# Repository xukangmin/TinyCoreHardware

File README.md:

# TinyCoreHardware
Hardware Files for Tiny Core

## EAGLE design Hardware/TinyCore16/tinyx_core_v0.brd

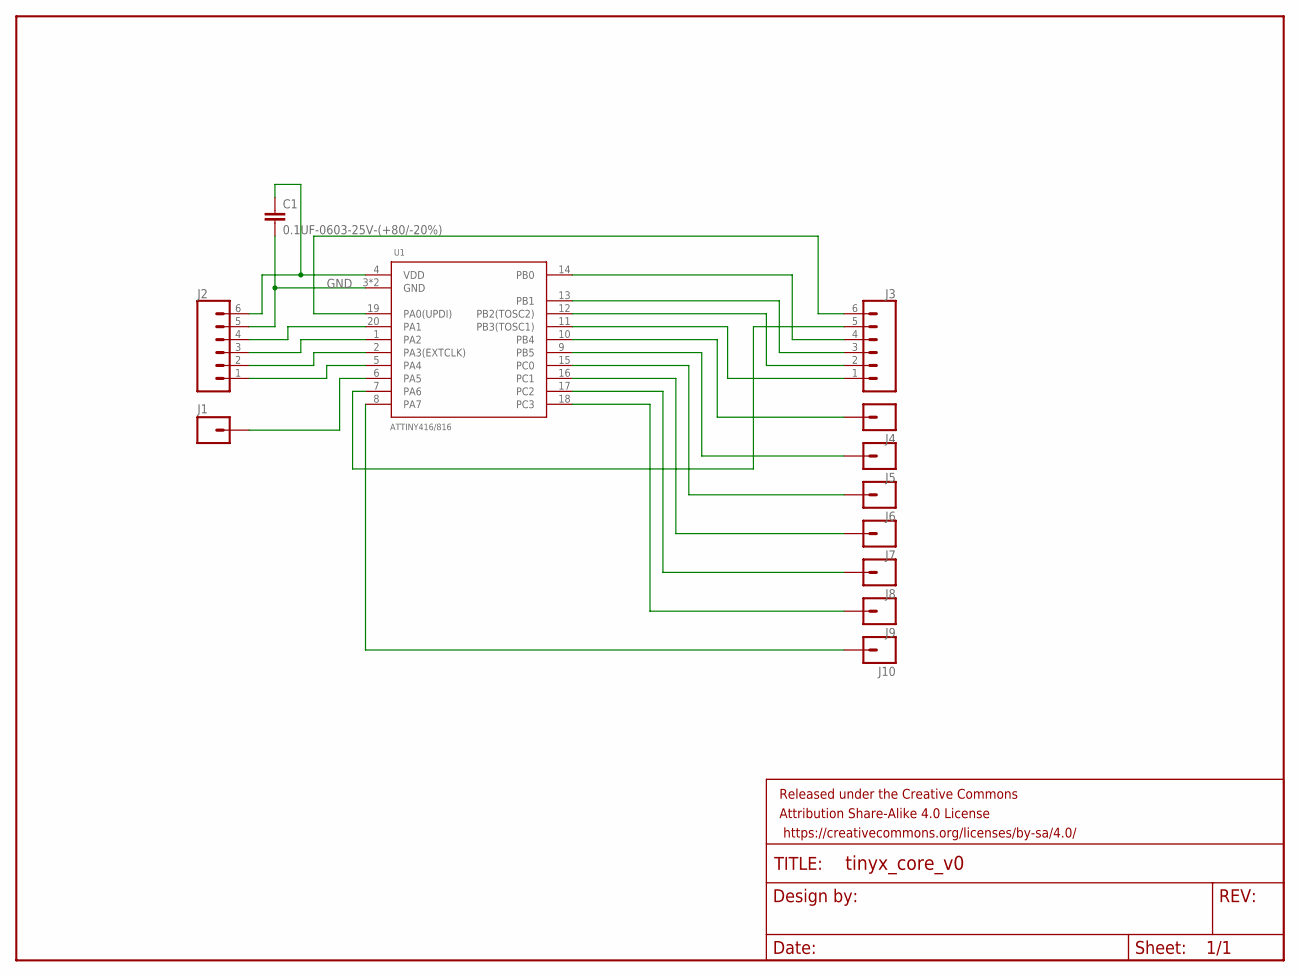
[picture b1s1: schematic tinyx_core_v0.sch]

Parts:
C1: 0.1UF-0603-25V-(+80/-20%); 0603
FRAME1: FRAME-LETTER; CREATIVE_COMMONS
J1, J4, J5, J6, J7, J8, J9, J10: M01TINY; 1X01_TINY
J2, J3: CONN_06NO_SILK_FEMALE_PTH; 1X06_NO_SILK
U1: ATTINY416/816; VQFN-20

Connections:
GND: C1.2, J2.5, U1.3 (GND), U1.EXP (GND)
unnamed: C1.1, J2.6, U1.4 (VDD)
unnamed: J2.4, U1.20 (PA1)
unnamed: J2.3, U1.1 (PA2)
unnamed: J2.2, U1.2 (PA3(EXTCLK))
unnamed: J2.1, U1.5 (PA4)
unnamed: J3.6, U1.19 (PA0(UPDI))
unnamed: J3.5, U1.7 (PA6)
unnamed: J3.4, U1.14 (PB0)
unnamed: J3.3, U1.13 (PB1)
unnamed: J3.2, U1.12 (PB2(TOSC2))
unnamed: J3.1, U1.11 (PB3(TOSC1))
unnamed: J1.P$1, U1.6 (PA5)
unnamed: J4.P$1, U1.10 (PB4)
unnamed: J5.P$1, U1.9 (PB5)
unnamed: J6.P$1, U1.15 (PC0)
unnamed: J7.P$1, U1.16 (PC1)
unnamed: J8.P$1, U1.17 (PC2)
unnamed: J9.P$1, U1.18 (PC3)
unnamed: J10.P$1, U1.8 (PA7)

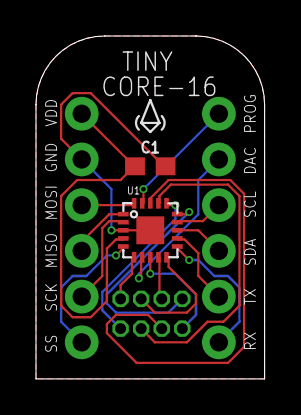
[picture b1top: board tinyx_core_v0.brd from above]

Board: 2 copper layers, 12.7 x 19.1 mm, 13 parts (0 on the bottom side), 20 nets.

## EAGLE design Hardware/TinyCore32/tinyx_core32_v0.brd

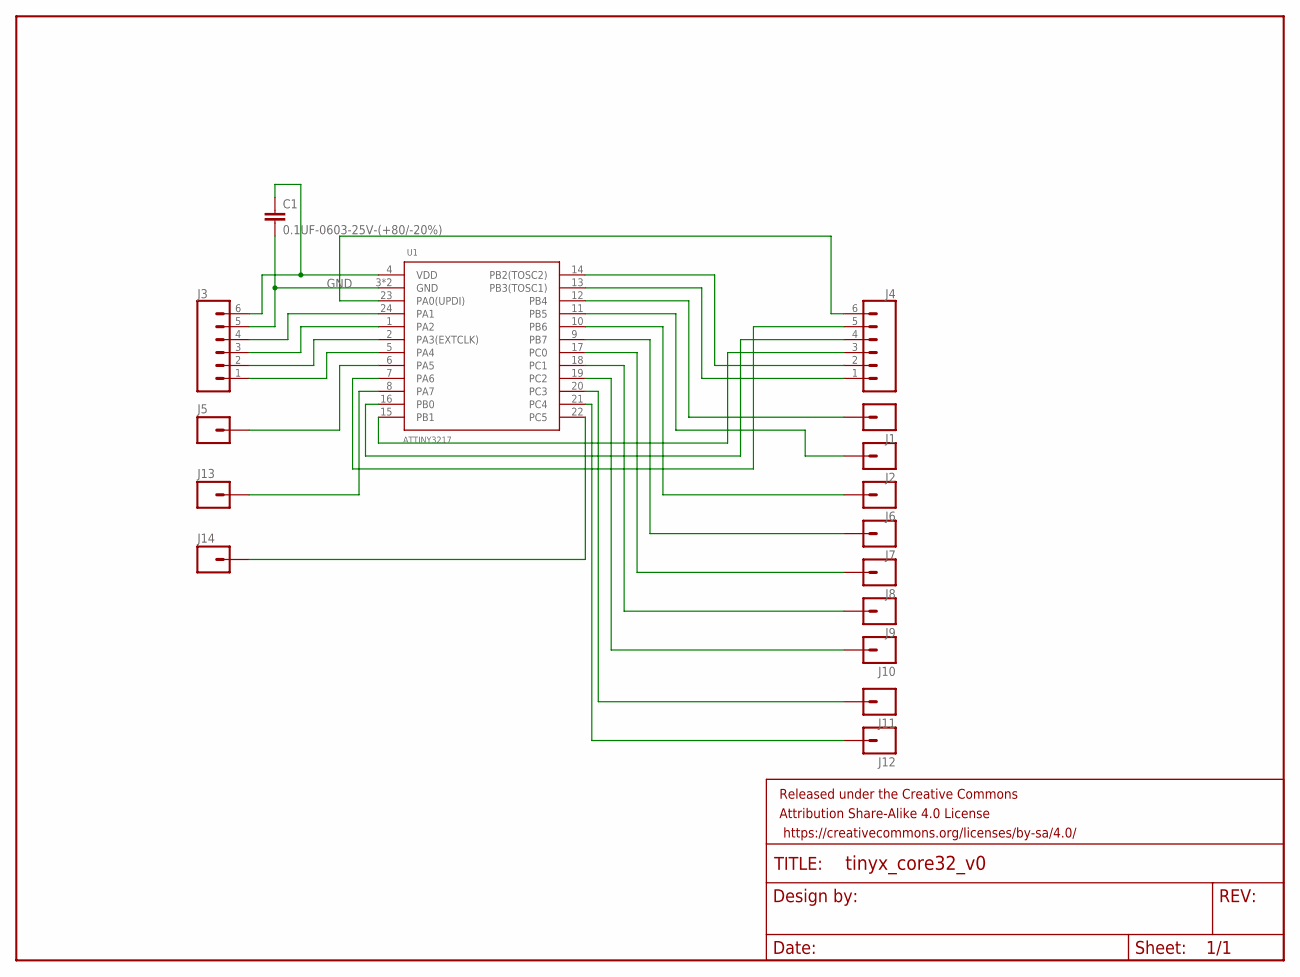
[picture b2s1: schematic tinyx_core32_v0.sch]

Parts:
C1: 0.1UF-0603-25V-(+80/-20%); 0603
FRAME1: FRAME-LETTER; CREATIVE_COMMONS
J1, J2, J5, J6, J7, J8, J9, J10, J11, J12, J13, J14: M01TINY; 1X01_TINY
J3, J4: CONN_06NO_SILK_NO_POP; 1X06_NO_SILK
U1: ATTINY3217; VQFN-24-N

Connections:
GND: C1.2, J3.5, U1.3 (GND), U1.P$1 (GND)
unnamed: C1.1, J3.6, U1.4 (VDD)
unnamed: J3.4, U1.24 (PA1)
unnamed: J3.3, U1.1 (PA2)
unnamed: J3.2, U1.2 (PA3(EXTCLK))
unnamed: J3.1, U1.5 (PA4)
unnamed: J4.6, U1.23 (PA0(UPDI))
unnamed: J1.P$1, U1.12 (PB4)
unnamed: J4.5, U1.7 (PA6)
unnamed: J4.4, U1.16 (PB0)
unnamed: J4.3, U1.15 (PB1)
unnamed: J4.2, U1.14 (PB2(TOSC2))
unnamed: J4.1, U1.13 (PB3(TOSC1))
unnamed: J5.P$1, U1.6 (PA5)
unnamed: J2.P$1, U1.11 (PB5)
unnamed: J13.P$1, U1.8 (PA7)
unnamed: J6.P$1, U1.10 (PB6)
unnamed: J7.P$1, U1.9 (PB7)
unnamed: J8.P$1, U1.17 (PC0)
unnamed: J9.P$1, U1.18 (PC1)
unnamed: J14.P$1, U1.22 (PC5)
unnamed: J10.P$1, U1.19 (PC2)
unnamed: J11.P$1, U1.20 (PC3)
unnamed: J12.P$1, U1.21 (PC4)

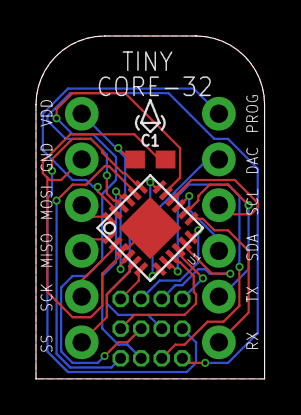
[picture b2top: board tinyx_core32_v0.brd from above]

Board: 2 copper layers, 12.7 x 19.1 mm, 17 parts (0 on the bottom side), 24 nets.

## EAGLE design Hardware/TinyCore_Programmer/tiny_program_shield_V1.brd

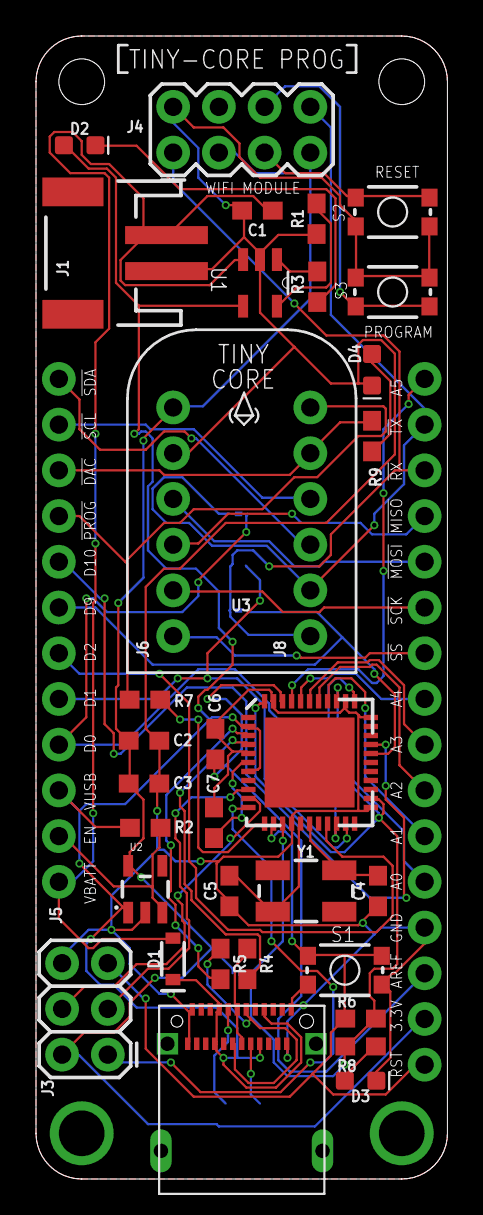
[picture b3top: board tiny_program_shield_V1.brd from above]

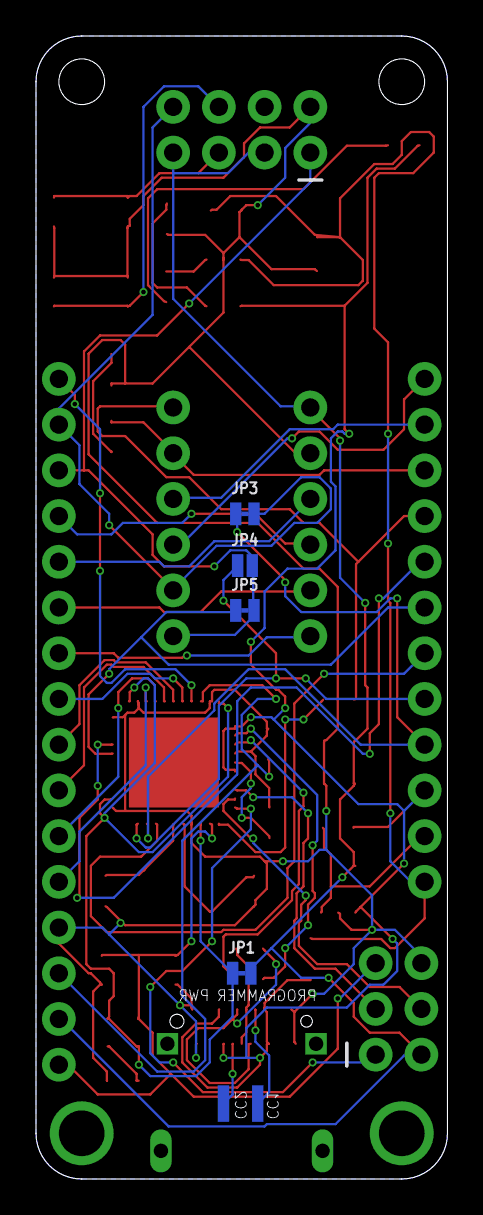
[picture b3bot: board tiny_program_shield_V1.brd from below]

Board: 2 copper layers, 22.9 x 63.5 mm, 44 parts (6 on the bottom side), 49 nets.

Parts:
C1, C2: 10uF; 0603
C3, C7: 1.0uF; 0603
C4, C5: 26pF; 0603
C6: 0.1uF; 0603
D1: SOD-323
D2: Yellow; LED-0603
D3: Green; LED-0603
D4: Blue; LED-0603
FRAME1: FRAME-LETTER; CREATIVE_COMMONS
H1, H2: MOUNT-PAD-ROUND0.1IN; 0.1-PAD
J1: JST-2-SMD
J2: USB-TYPE-C; USB-C-AMPHENOL
J3: 2X3
J4: 2X4
J5: 1X12_NO_SILK
J6, J8: 1X06_NO_SILK
J7, J10: 1X01_SMD_TINY
J9: 1X16_NO_SILK
JP1, JP3, JP5: JUMPER-SMT_2_NC_TRACE_NO-SILK; SMT-JUMPER_2_NC_TRACE_NO-SILK
JP4: JUMPER-SMT_2_NO_NO-SILK; SMT-JUMPER_2_NO_NO-SILK
R1, R6: 10K; 0603
R2: 100K; 0603
R3, R8: 1K; 0603
R4, R5: 22; 0603
R7: 4.7K; 0603
R9: 100; 0603
S1, S2, S3: SWITCH-MOMENTARY-2SMD-4.6X2.8MM; TACTILE_SWITCH_SMD_4.6X2.8MM
U1: MCP73831T-4ADI/OT; SOT95P280X145-5N
U2: SPX3819M5_3_3; SOT23-5
U3: 32U4; QFN-44
Y1: 8MHz; CRYSTAL-SMD-5X3.2-4PAD

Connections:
3.3V: C2.1, C3.1, J3.2, J4.3, J4.7, J6.6, J9.2, JP1.2, U2.5
A0: J9.5, U3.36
A1: J9.6, U3.37
A2: J9.7, U3.38
A3: J9.8, U3.39
A4: J9.9, U3.40
A5: J9.16, U3.41
AREF: C6.1, J9.3, U3.42
CC1: J2.A5, J7.P$1
CC2: J2.B5, J10.P$1
CORE_MISO: J6.3, J9.13
CORE_MOSI: J6.4, J9.12
CORE_RX: J4.1, J8.1, J9.14, JP4.2, JP5.2
CORE_SCK: J6.2, J9.11
CORE_SCL: J5.11, J8.4
CORE_SDA: J5.12, J8.3
CORE_SS: J6.1, J9.10
CORE_TX: J4.8, J8.2, J9.15, JP3.2
D0: J5.4, JP3.1, U3.20
D1: J5.5, JP4.1, U3.21
D2: J5.6, U3.19
D9: J5.7, JP5.1, U3.29
D10: J5.8, U3.30
DAC/AIN6: J5.10, J8.5, R9.1
EN: J5.2, R2.2, U2.3
GND: C1.2, C2.2, C3.2, C4.1, C5.1, C6.2, C7.2, D3.C, D4.C, J1.1, J2.A1, J2.A12, J2.B1, J2.B12, J3.6, J4.2, J6.5, J9.4, R1.1, S1.3, S1.4, S2.3, S2.4, S3.1, S3.2, U1.2, U2.2, U3.5, U3.15, U3.23, U3.33, U3.35, U3.43
MISO: J3.1, U3.11
MOSI: J3.4, U3.10
unnamed: J2.A6, J2.B6, R4.1
unnamed: J2.A7, J2.B7, R5.1
unnamed: R4.2, U3.4
unnamed: R5.2, U3.3
unnamed: C4.2, U3.17, Y1.3
unnamed: C5.2, U3.16, Y1.1
unnamed: R1.2, U1.5
unnamed: R3.1, U1.1
unnamed: D2.C, R3.2
unnamed: C7.1, U3.6
unnamed: J4.5, S2.1, S2.2
unnamed: R7.1, U3.12
unnamed: J4.6, S3.3, S3.4
unnamed: JP1.1, R6.1, R8.2, U3.14, U3.24, U3.34, U3.44
unnamed: D3.A, R8.1
unnamed: D4.A, R9.2
PROG: J5.9, J8.6, R7.2
RST: J3.5, J9.1, R6.2, S1.1, S1.2, U3.13
SCK: J3.3, U3.9
V_BATT: C1.1, D1.A, J1.2, J5.1, U1.3
V_USB: D1.C, D2.A, J2.A4, J2.A9, J2.B4, J2.B9, J5.3, R2.1, U1.4, U2.1, U3.2, U3.7

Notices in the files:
parts and their libraries:
SparkFun-Connectors: Licensing: Creative Commons ShareAlike 4.0 International - https://creativecommons.org/licenses/by-sa/4.0
SparkFun-Aesthetics: Released under the Creative Commons Attribution Share-Alike 4.0 License
SparkFun-Aesthetics: https://creativecommons.org/licenses/by-sa/4.0
